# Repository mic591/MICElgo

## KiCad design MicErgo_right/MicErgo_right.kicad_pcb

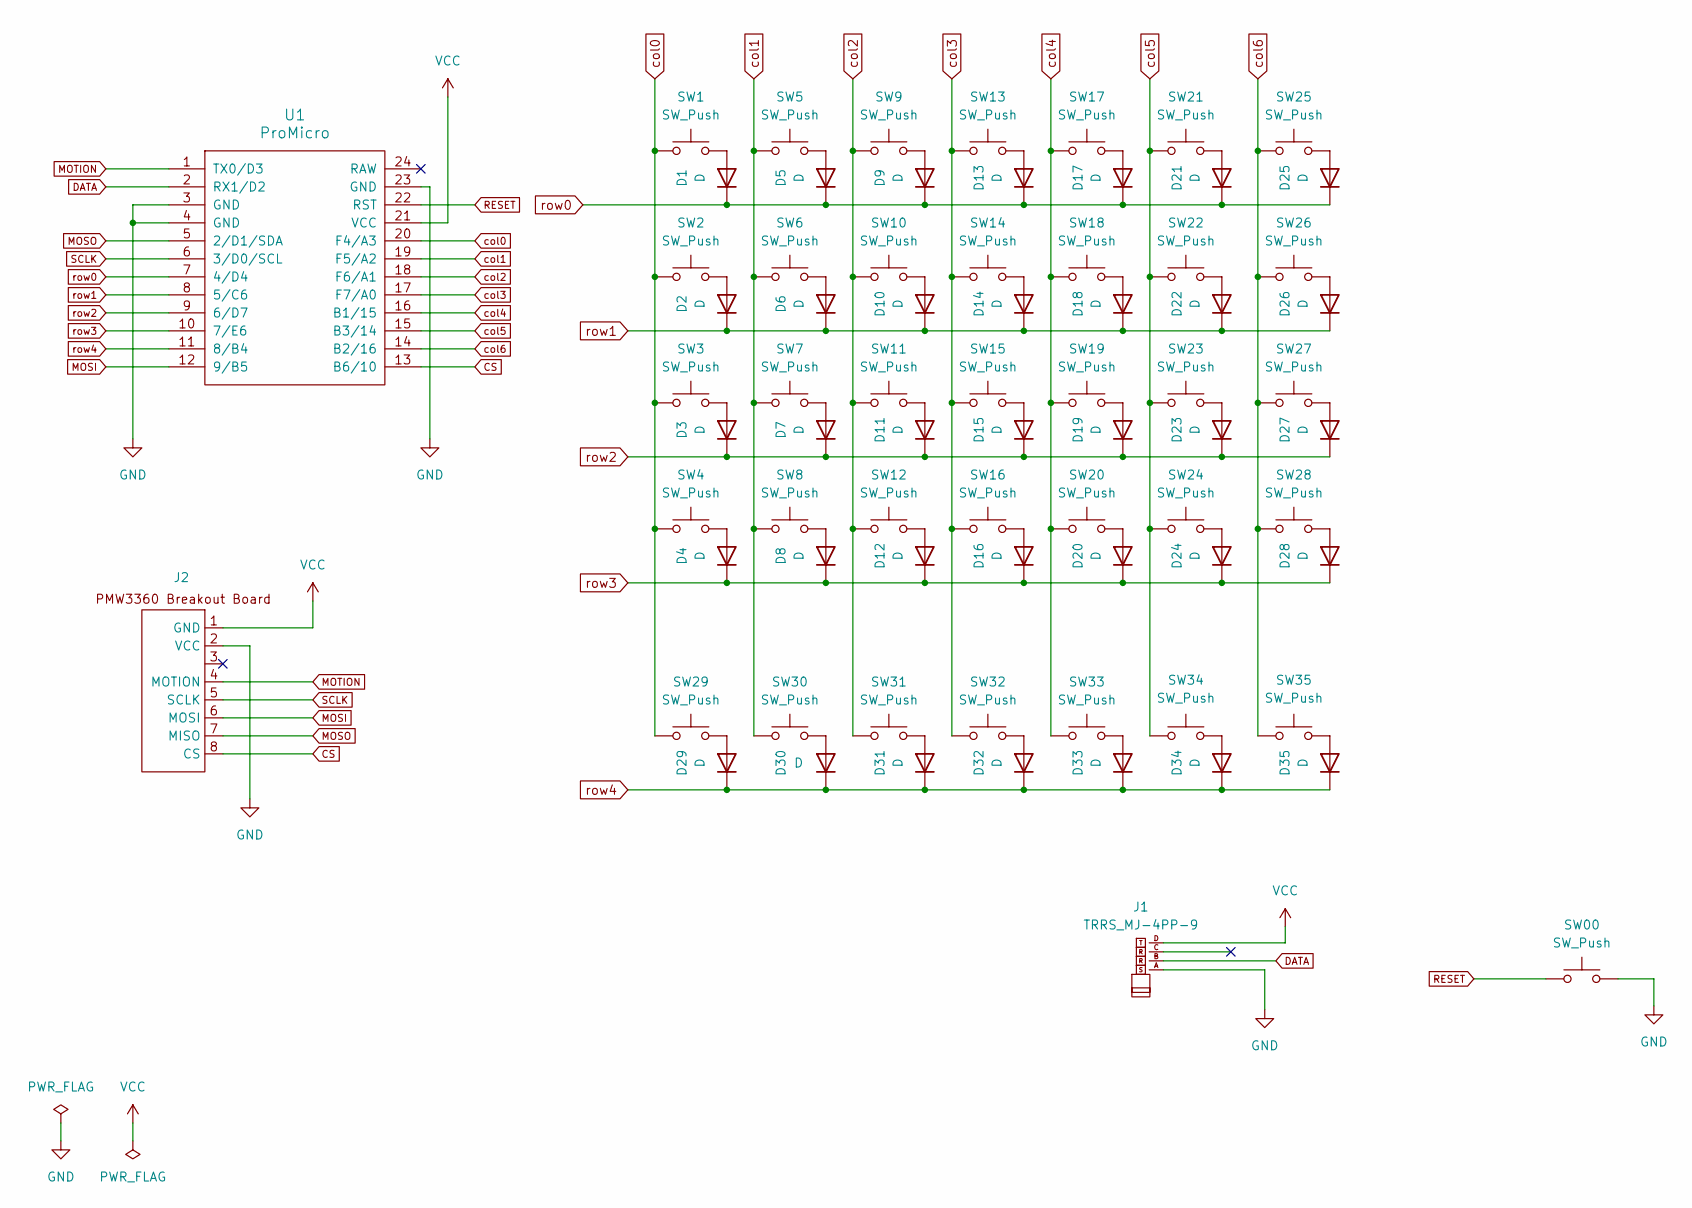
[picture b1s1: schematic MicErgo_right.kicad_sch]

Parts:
D1, D2, D3, D4, D5, D6, D7, D8, D9, D10, D11, D12, D13, D14, D15, D16, D17, D18, D19, D20, D21, D22, D23, D24, D25, D26, D27, D28, D29, D30, D31, D32, D33, D34, D35: D; Diode_SMD_top
J1: TRRS_MJ-4PP-9
J2: PMW3360
SW00: SW_Push; ResetSW
SW1, SW2, SW3, SW4, SW5, SW6, SW7, SW8, SW9, SW10, SW11, SW12, SW13, SW14, SW15, SW16, SW17, SW18, SW19, SW20, SW21, SW22, SW23, SW24, SW25, SW26, SW27, SW28, SW29, SW30, SW31, SW32, SW33, SW34, SW35: SW_Push; Choc_v2_Hotswap_1u_Narrow
U1: ProMicro; Micon_ProMicro

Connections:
CS: J2.8 (CS), U1.13 (B6/10)
DATA: J1.B, U1.2 (RX1/D2)
GND: J1.A, J2.2 (VCC), SW00.2, U1.3 (GND), U1.4 (GND), U1.23 (GND)
MOSI: J2.6 (MOSI), U1.12 (9/B5)
MOSO: J2.7 (MISO), U1.5 (2/D1/SDA)
MOTION: J2.4 (MOTION), U1.1 (TX0/D3)
unnamed: D1.2 (A), SW1.2
unnamed: D2.2 (A), SW2.2
unnamed: D3.2 (A), SW3.2
unnamed: D4.2 (A), SW4.2
unnamed: D5.2 (A), SW5.2
unnamed: D6.2 (A), SW6.2
unnamed: D7.2 (A), SW7.2
unnamed: D8.2 (A), SW8.2
unnamed: D9.2 (A), SW9.2
unnamed: D10.2 (A), SW10.2
unnamed: D11.2 (A), SW11.2
unnamed: D12.2 (A), SW12.2
unnamed: D13.2 (A), SW13.2
unnamed: D14.2 (A), SW14.2
unnamed: D15.2 (A), SW15.2
unnamed: D16.2 (A), SW16.2
unnamed: D17.2 (A), SW17.2
unnamed: D18.2 (A), SW18.2
unnamed: D19.2 (A), SW19.2
unnamed: D20.2 (A), SW20.2
unnamed: D21.2 (A), SW21.2
unnamed: D22.2 (A), SW22.2
unnamed: D23.2 (A), SW23.2
unnamed: D24.2 (A), SW24.2
unnamed: D25.2 (A), SW25.2
unnamed: D26.2 (A), SW26.2
unnamed: D27.2 (A), SW27.2
unnamed: D28.2 (A), SW28.2
unnamed: D29.2 (A), SW29.2
unnamed: D30.2 (A), SW30.2
unnamed: D31.2 (A), SW31.2
unnamed: D32.2 (A), SW32.2
unnamed: D33.2 (A), SW33.2
unnamed: D34.2 (A), SW34.2
unnamed: D35.2 (A), SW35.2
RESET: SW00.1, U1.22 (RST)
SCLK: J2.5 (SCLK), U1.6 (3/D0/SCL)
VCC: J1.D, J2.1 (GND), U1.21 (VCC)
col0: SW1.1, SW2.1, SW3.1, SW4.1, SW29.1, U1.20 (F4/A3)
col1: SW5.1, SW6.1, SW7.1, SW8.1, SW30.1, U1.19 (F5/A2)
col2: SW9.1, SW10.1, SW11.1, SW12.1, SW31.1, U1.18 (F6/A1)
col3: SW13.1, SW14.1, SW15.1, SW16.1, SW32.1, U1.17 (F7/A0)
col4: SW17.1, SW18.1, SW19.1, SW20.1, SW33.1, U1.16 (B1/15)
col5: SW21.1, SW22.1, SW23.1, SW24.1, SW34.1, U1.15 (B3/14)
col6: SW25.1, SW26.1, SW27.1, SW28.1, SW35.1, U1.14 (B2/16)
row0: D1.1 (K), D5.1 (K), D9.1 (K), D13.1 (K), D17.1 (K), D21.1 (K), D25.1 (K), U1.7 (4/D4)
row1: D2.1 (K), D6.1 (K), D10.1 (K), D14.1 (K), D18.1 (K), D22.1 (K), D26.1 (K), U1.8 (5/C6)
row2: D3.1 (K), D7.1 (K), D11.1 (K), D15.1 (K), D19.1 (K), D23.1 (K), D27.1 (K), U1.9 (6/D7)
row3: D4.1 (K), D8.1 (K), D12.1 (K), D16.1 (K), D20.1 (K), D24.1 (K), D28.1 (K), U1.10 (7/E6)
row4: D29.1 (K), D30.1 (K), D31.1 (K), D32.1 (K), D33.1 (K), D34.1 (K), D35.1 (K), U1.11 (8/B4)

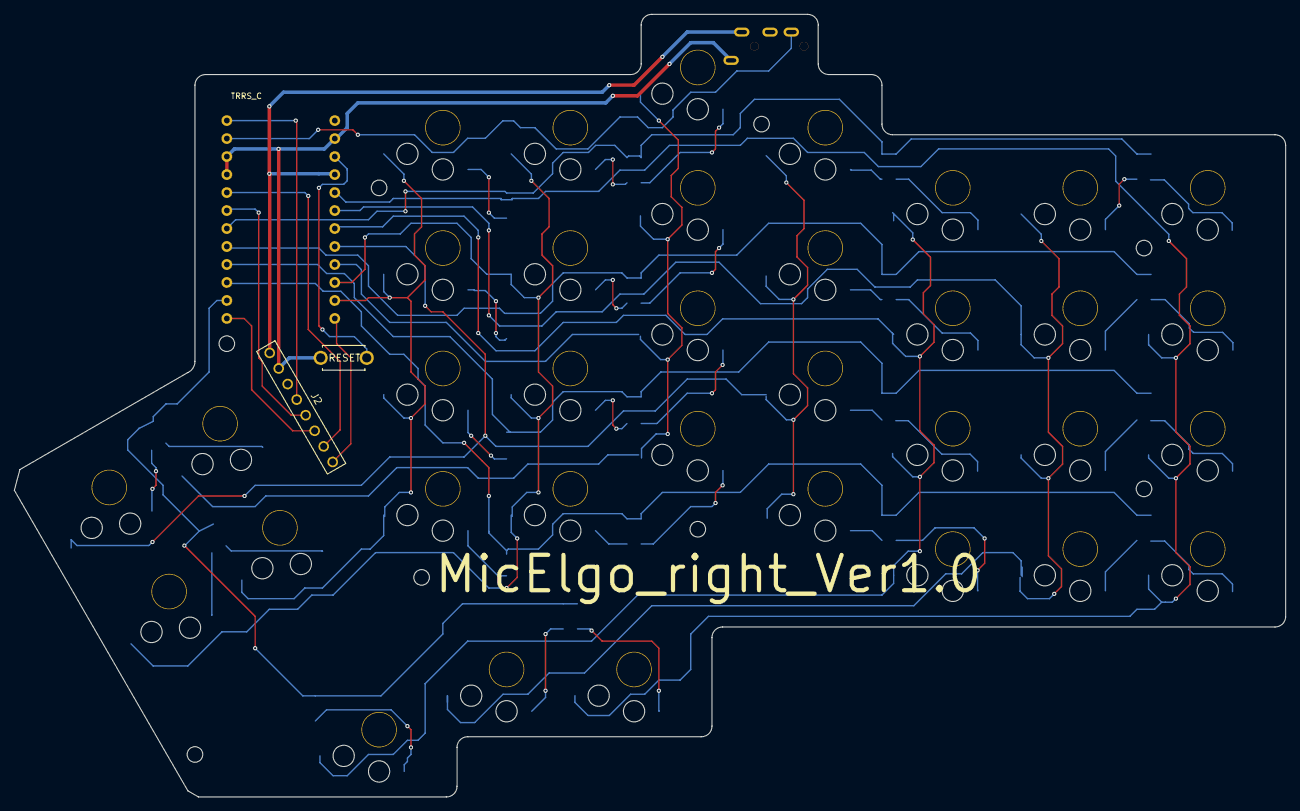
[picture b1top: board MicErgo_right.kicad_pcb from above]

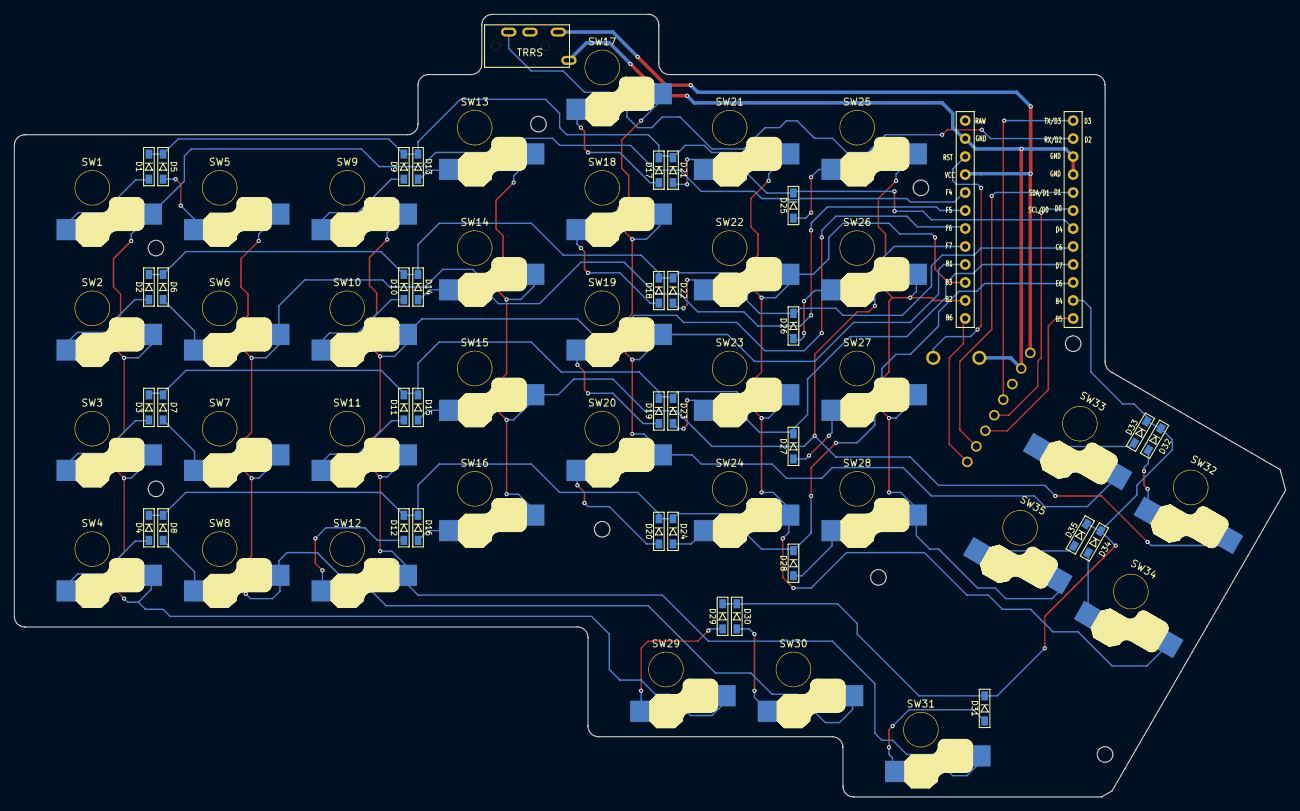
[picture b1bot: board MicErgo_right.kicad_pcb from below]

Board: 2 copper layers, 179.5 x 110.5 mm, 82 parts (79 on the bottom side), 56 nets.

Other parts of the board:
Ref**: Val**; m2_Screw_Hole
Ref**#2, Ref**#3, Ref**#4, Ref**#5, Ref**#6, Ref**#7, Ref**#8: Val**; m2_Screw_Hole
